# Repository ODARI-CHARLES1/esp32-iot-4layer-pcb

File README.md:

# ESP32 IoT 4-Layer PCB

This project focuses on the design and development of a **4-layer PCB** for an **ESP32-based IoT device**. The goal is to create a compact, robust, and EMI-optimized PCB layout suitable for IoT applications.

---

###### Power Management

###### Microcontroller, USB_UART, FLASH MEMORY AND SD CARD

## Project Overview

- **Microcontroller:** ESP32-WROOM-32 (or compatible module)
- **PCB Layers:** 4 (Signal–Ground–Power–Signal stackup)
- **Purpose:** General-purpose IoT hardware platform for prototyping and deployment
- **Tools Used:** KiCad (v6/v7), Git for version control

---

## Design Highlights

- **4-layer stackup** for improved signal integrity and reduced EMI
- Compact layout with modular headers for sensors and peripherals
- On-board voltage regulation (LDO or buck converter)
- USB-to-UART for programming and debugging
- Decoupling and impedance control best practices
- Optional: Antenna matching network for Wi-Fi/BLE

---

---

## Work in Progress

- [X] Schematic capture
- [X] 4-layer stackup definition
- [x] Final PCB layout
- [x] DRC/clearance verification
- [ ] Gerber export and fabrication
- [ ] Testing and validation

---

## Getting Started

1. Open the project in **KiCad v6 or later**
2. Explore `*.kicad_sch` and `*.kicad_pcb` files
3. Run DRC/ERC checks
4. Generate or review the BOM and Gerbers
5. Export fabrication files for PCB manufacturing

---

## Bill of Materials (BOM)

The complete BOM is available in [`Docs/PROJECT_PCB.csv`](Docs/PROJECT_PCB.csv). This file contains all components required for the PCB assembly, including quantities, values, footprints, and datasheets.

Key components include:

- **ESP32-C3-WROOM-02**: Main microcontroller module
- **CP2102N**: USB-to-UART bridge for programming
- **MCP73871**: Battery charging IC
- **W25Q16JVSS**: 16MB flash memory
- Various capacitors, resistors, LEDs, and connectors

---

## Documentation

- **Schematic PDF**: [`Docs/schematic.pdf`](Docs/schematic.pdf)
- **KiCad Project Files**: See `.kicad_sch` and `.kicad_pcb` files in the repository

---

## Previews

_3D renders, board stackup diagrams, or layout screenshots can go here_

---

## License

This project is open source under the **MIT License** (or specify yours).
Feel free to use, modify, and contribute.

---

## Contributions

Issues, suggestions, and pull requests are welcome!
If you'd like to contribute hardware improvements, please fork and submit a PR.

---

## Contact

Questions or feedback? Reach out via GitHub Issues or email: `daymondodari68@gmail.com`

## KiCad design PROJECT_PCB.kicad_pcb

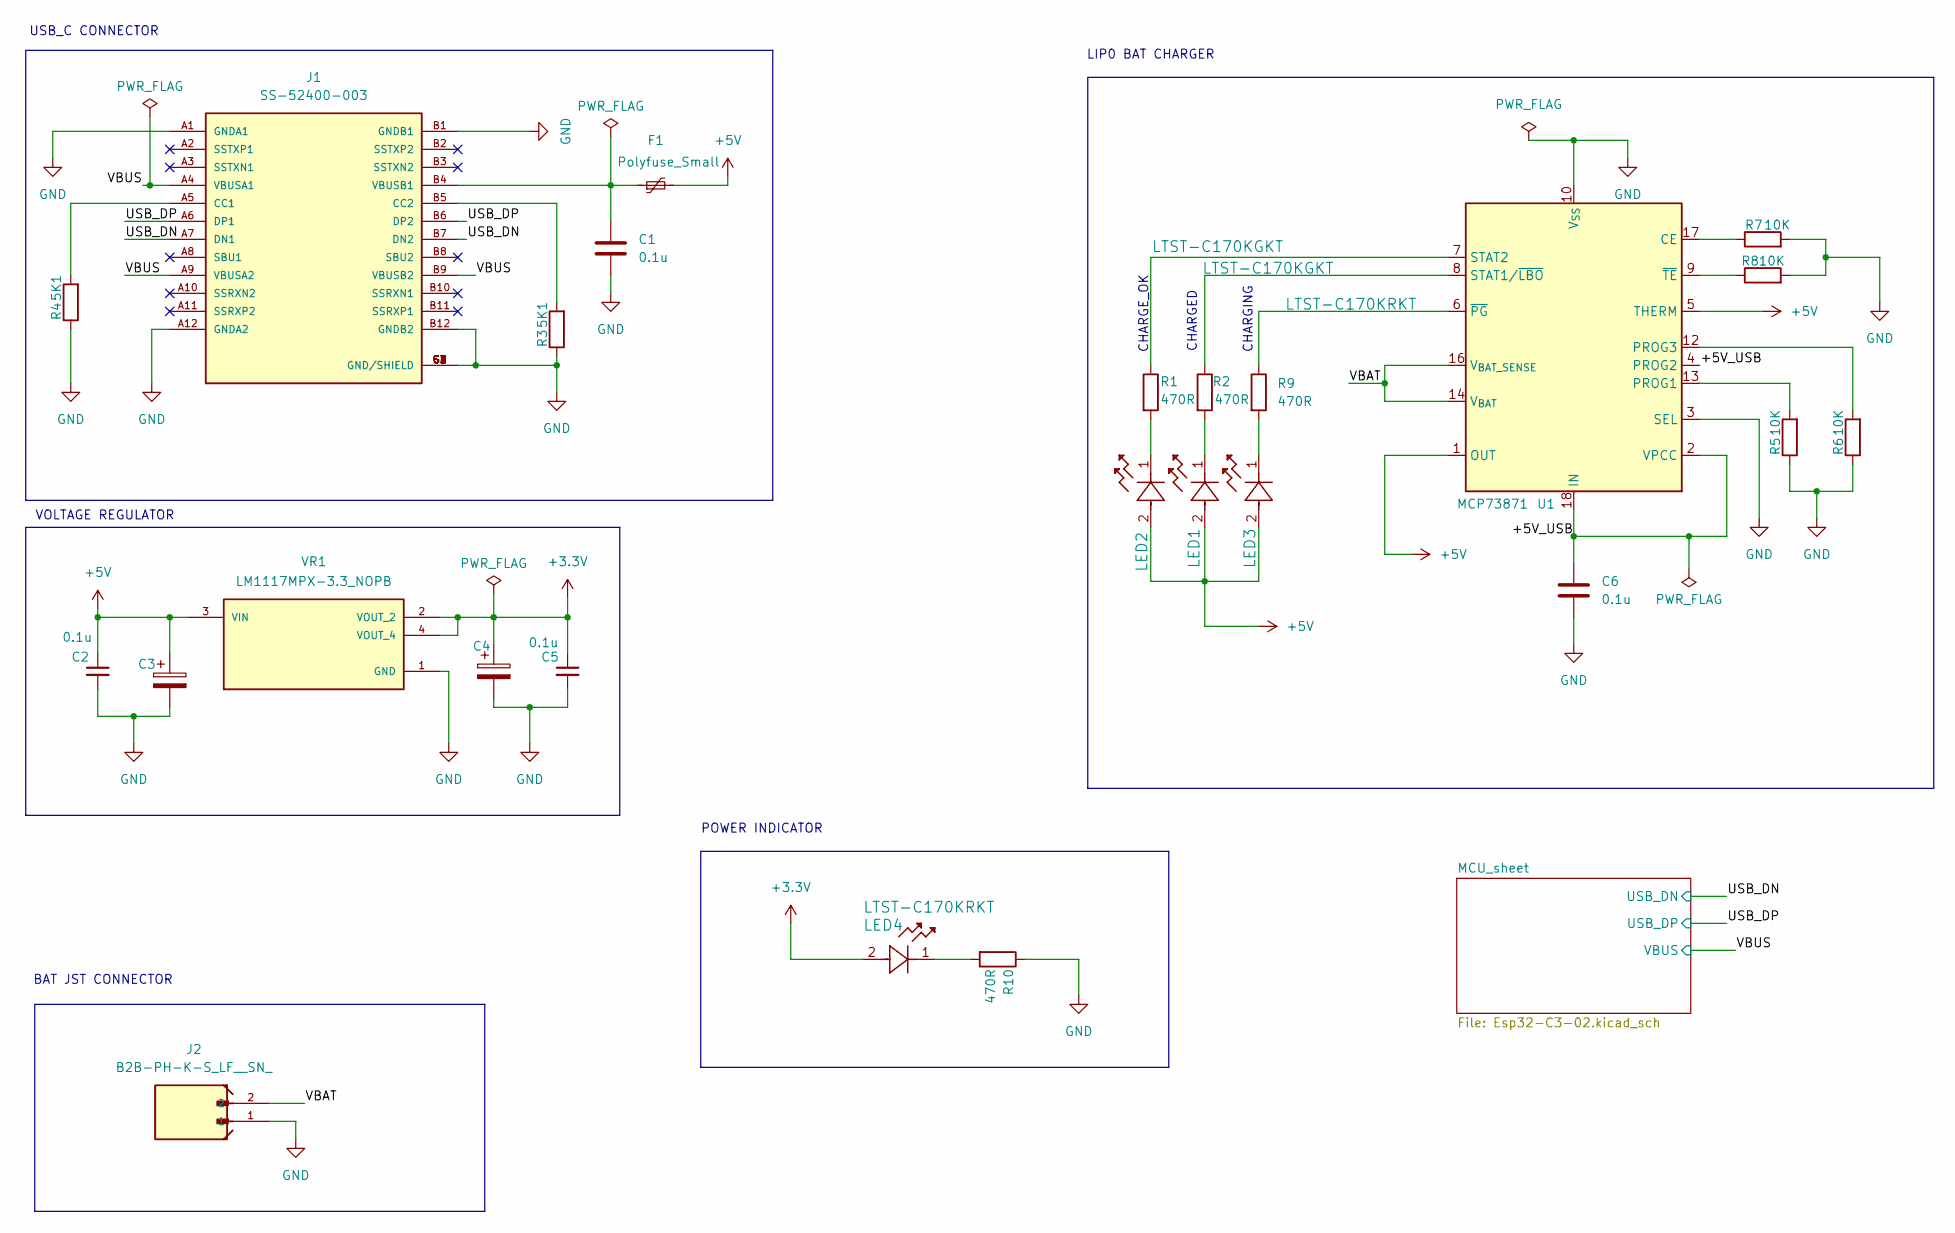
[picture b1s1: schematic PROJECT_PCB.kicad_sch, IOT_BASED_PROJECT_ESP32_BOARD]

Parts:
C1, C2, C5, C6: 0.1u; C_0805_2012Metric
C3, C4: 10u; CAPMP3216X180N
F1: Polyfuse_Small; Fuse_BelFuse_0ZRE0016FF_L9.9mm_W3.8mm
J1: SS-52400-003; BELFUSE_SS-52400-003; Manufacturer part Number SS-52400-003; LCSC C6301911
J2: B2B-PH-K-S_LF__SN_; JST_B2B-PH-K-S_LF__SN_
LED1, LED2: LTST-C170KGKT; LED_0805_2012Metric
LED3, LED4: LTST-C170KRKT; LED_0805_2012Metric
R1, R2, R9, R10: 470R; R_0805_2012Metric
R3, R4: 5K1; R_0805_2012Metric
R5, R6, R7, R8: 10K; R_0805_2012Metric
U1: MCP73871; QFN-20-1EP_4x4mm_P0.5mm_EP2.5x2.5mm
VR1: LM1117MPX-3.3_NOPB; VREG_LM1117MPX-3.3_NOPB; Manufacturer part Number LM1117MPX-3.3/NOPB; LCSC C9662

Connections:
+3.3V: C4.1, C5.1, LED4.2, VR1.2 (VOUT_2), VR1.4 (VOUT_4); also elsewhere on the board
+5V: C2.1, C3.1, F1.2, LED1.2, LED2.2, LED3.2, U1.1 (OUT), U1.5 (THERM), U1.20 (OUT), VR1.3 (VIN)
/+5V_USB: C6.1, U1.2 (VPCC), U1.4 (PROG2), U1.18 (IN), U1.19 (IN)
/USB_DN: J1.A7 (DN1), J1.B7 (DN2); also elsewhere on the board
/USB_DP: J1.A6 (DP1), J1.B6 (DP2); also elsewhere on the board
/VBAT: J2.2, U1.14 (V_{BAT}), U1.15 (V_{BAT}), U1.16 (V_{BAT_SENSE})
/VBUS: J1.A4 (VBUSA1), J1.A9 (VBUSA2), J1.B9 (VBUSB2); also elsewhere on the board
GND: C1.2, C2.2, C3.2, C4.2, C5.2, C6.2, J1.A1 (GNDA1), J1.A12 (GNDA2), J1.B1 (GNDB1), J1.B12 (GNDB2), J1.G1 (GND/SHIELD), J1.G2 (GND/SHIELD), J1.G3 (GND/SHIELD), J1.G4 (GND/SHIELD), J1.S1 (GND/SHIELD), J1.S2 (GND/SHIELD), J1.S3 (GND/SHIELD), J1.S4 (GND/SHIELD), J2.1, R3.1, R4.1, R5.1, R6.1, R7.2, R8.2, R10.1, U1.3 (SEL), U1.10 (V_{SS}), U1.11 (V_{SS}), U1.21 (V_{SS}), VR1.1 (GND); also elsewhere on the board
unnamed: J1.A5 (CC1), R4.2
unnamed: J1.B5 (CC2), R3.2
unnamed: C1.1, F1.1, J1.B4 (VBUSB1)
unnamed: LED1.1, R2.2
unnamed: LED2.1, R1.2
unnamed: LED3.1, R9.2
unnamed: LED4.1, R10.2
unnamed: R7.1, U1.17 (CE)
unnamed: R5.2, U1.13 (PROG1)
unnamed: R6.2, U1.12 (PROG3)
unnamed: R2.1, U1.8 (STAT1/~LBO)
unnamed: R1.1, U1.7 (STAT2)
unnamed: R9.1, U1.6 (~PG)
unnamed: R8.1, U1.9 (~TE)

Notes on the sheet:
LIP0 BAT CHARGER
CHARGE_OK
CHARGED
BAT JST CONNECTOR
VOLTAGE REGULATOR
POWER INDICATOR
CHARGING
USB_C CONNECTOR

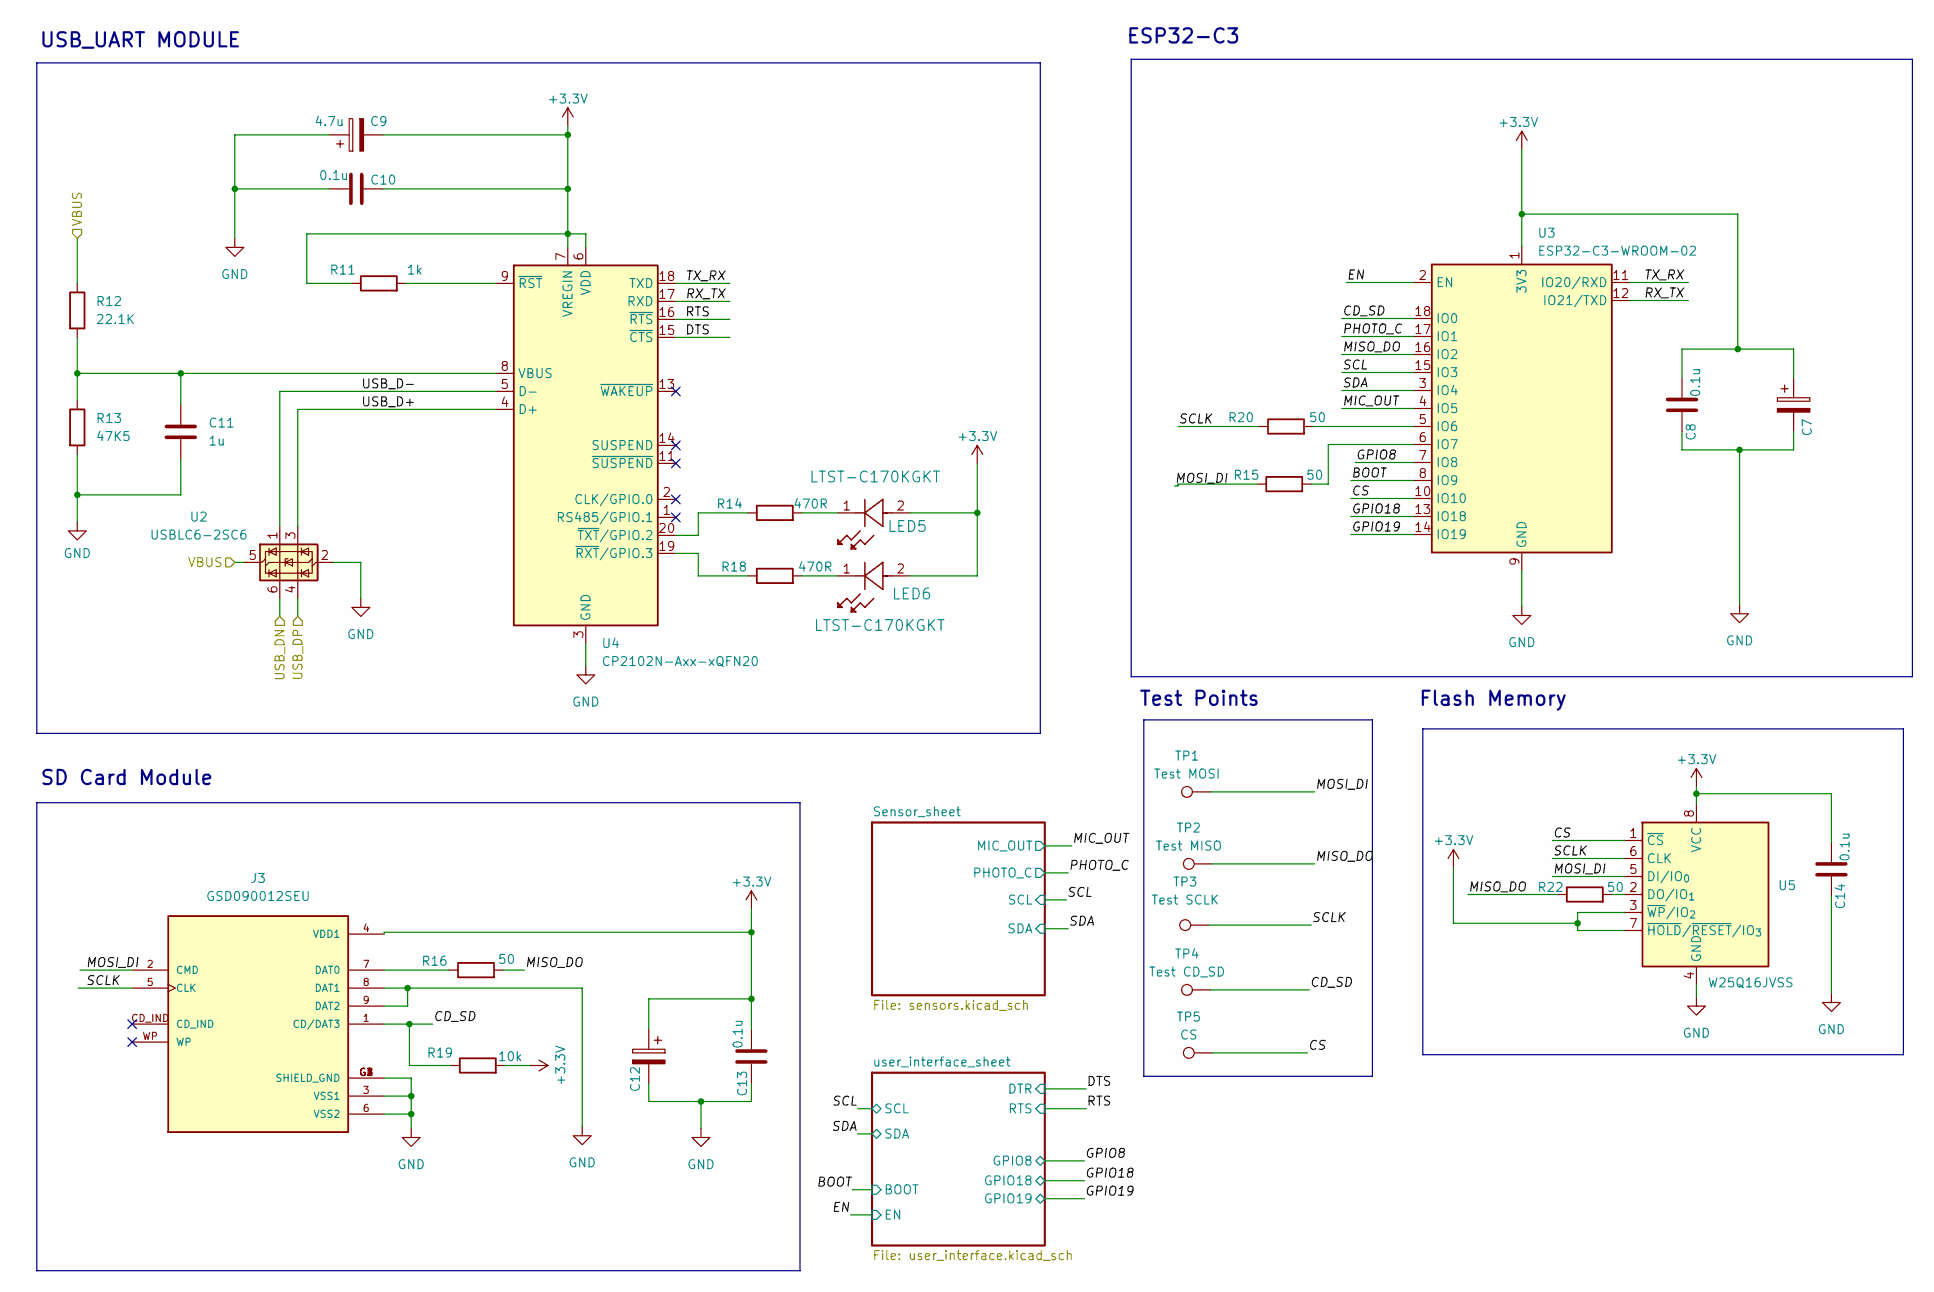
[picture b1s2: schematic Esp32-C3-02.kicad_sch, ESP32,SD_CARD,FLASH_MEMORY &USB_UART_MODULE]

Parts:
C7, C12: 10u; CP_EIA-7343-40_Kemet-Y
C8, C10, C13, C14: 0.1u; C_0805_2012Metric
C9: 4.7u; CP_EIA-7343-40_Kemet-Y
C11: 1u; C_0805_2012Metric
J3: GSD090012SEU; AMPHENOL_GSD090012SEU; PARTREV E
LED5, LED6: LTST-C170KGKT; LED_0805_2012Metric
R11: 1k; R_0805_2012Metric
R12: 22.1K; R_0805_2012Metric
R13: 47K5; R_0805_2012Metric
R14, R18: 470R; R_0805_2012Metric
R15, R16, R20, R22: 50; R_0805_2012Metric
R19: 10k; R_0805_2012Metric
TP1: Test MOSI; TestPoint_Pad_D1.0mm
TP2: Test MISO; TestPoint_Pad_D1.0mm
TP3: Test SCLK; TestPoint_Pad_D1.0mm
TP4: Test CD_SD; TestPoint_Pad_D1.0mm
TP5: CS; TestPoint_Pad_D1.0mm
U2: USBLC6-2SC6; SOT-23-6
U3: ESP32-C3-WROOM-02
U4: CP2102N-Axx-xQFN20; SiliconLabs_QFN-20-1EP_3x3mm_P0.5mm
U5: W25Q16JVSS; SOIC-8_5.3x5.3mm_P1.27mm

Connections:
+3.3V: C7.1, C8.1, C9.2, C10.2, C12.1, C13.1, C14.1, J3.4 (VDD1), LED5.2, LED6.2, R11.1, R19.2, U3.1 (3V3), U4.6 (VDD), U4.7 (VREGIN), U5.3 (~WP/IO_{2}), U5.7 (~HOLD/~RESET/IO_{3}), U5.8 (VCC); also elsewhere on the board
/MCU_sheet/BOOT: U3.8 (IO9); also elsewhere on the board
/MCU_sheet/CD_SD: J3.1 (CD/DAT3), R19.1, TP4.1, U3.18 (IO0)
/MCU_sheet/CS: TP5.1, U3.10 (IO10), U5.1 (~CS)
/MCU_sheet/DTS: U4.15 (~CTS); also elsewhere on the board
/MCU_sheet/EN: U3.2 (EN); also elsewhere on the board
/MCU_sheet/GPIO8: U3.7 (IO8); also elsewhere on the board
/MCU_sheet/GPIO18: U3.13 (IO18); also elsewhere on the board
/MCU_sheet/GPIO19: U3.14 (IO19); also elsewhere on the board
/MCU_sheet/MIC_OUT: U3.4 (IO5); also elsewhere on the board
/MCU_sheet/MISO_DO: R16.2, R22.1, TP2.1, U3.16 (IO2)
/MCU_sheet/MOSI_DI: J3.2 (CMD), R15.1, TP1.1, U5.5 (DI/IO_{0})
/MCU_sheet/PHOTO_C: U3.17 (IO1); also elsewhere on the board
/MCU_sheet/RTS: U4.16 (~RTS); also elsewhere on the board
/MCU_sheet/RX_TX: U3.12 (IO21/TXD), U4.17 (RXD)
/MCU_sheet/SCL: U3.15 (IO3); also elsewhere on the board
/MCU_sheet/SCLK: J3.5 (CLK), R20.1, TP3.1, U5.6 (CLK)
/MCU_sheet/SDA: U3.3 (IO4); also elsewhere on the board
/MCU_sheet/TX_RX: U3.11 (IO20/RXD), U4.18 (TXD)
/MCU_sheet/USB_D+: U2.3 (I/O2), U4.4 (D+)
/MCU_sheet/USB_D-: U2.1 (I/O1), U4.5 (D-)
/USB_DN: U2.6 (I/O1); also elsewhere on the board
/USB_DP: U2.4 (I/O2); also elsewhere on the board
/VBUS: R12.1, U2.5 (VBUS); also elsewhere on the board
GND: C7.2, C8.2, C9.1, C10.1, C11.2, C12.2, C13.2, C14.2, J3.3 (VSS1), J3.6 (VSS2), J3.8 (DAT1), J3.9 (DAT2), J3.G1 (SHIELD_GND), J3.G2 (SHIELD_GND), J3.G3 (SHIELD_GND), J3.G4 (SHIELD_GND), R13.2, U2.2 (GND), U3.9 (GND), U3.19 (GND), U4.3 (GND), U4.12 (GND), U4.21 (GND), U5.4 (GND); also elsewhere on the board
unnamed: J3.7 (DAT0), R16.1
unnamed: LED5.1, R14.2
unnamed: LED6.1, R18.2
unnamed: R20.2, U3.5 (IO6)
unnamed: R15.2, U3.6 (IO7)
unnamed: C11.1, R12.2, R13.1, U4.8 (VBUS)
unnamed: R11.2, U4.9 (~RST)
unnamed: R18.1, U4.19 (~RXT/GPIO.3)
unnamed: R14.1, U4.20 (~TXT/GPIO.2)
unnamed: R22.2, U5.2 (DO/IO_{1})

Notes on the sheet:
SD Card Module
Test Points
USB_UART MODULE
Flash Memory
ESP32-C3

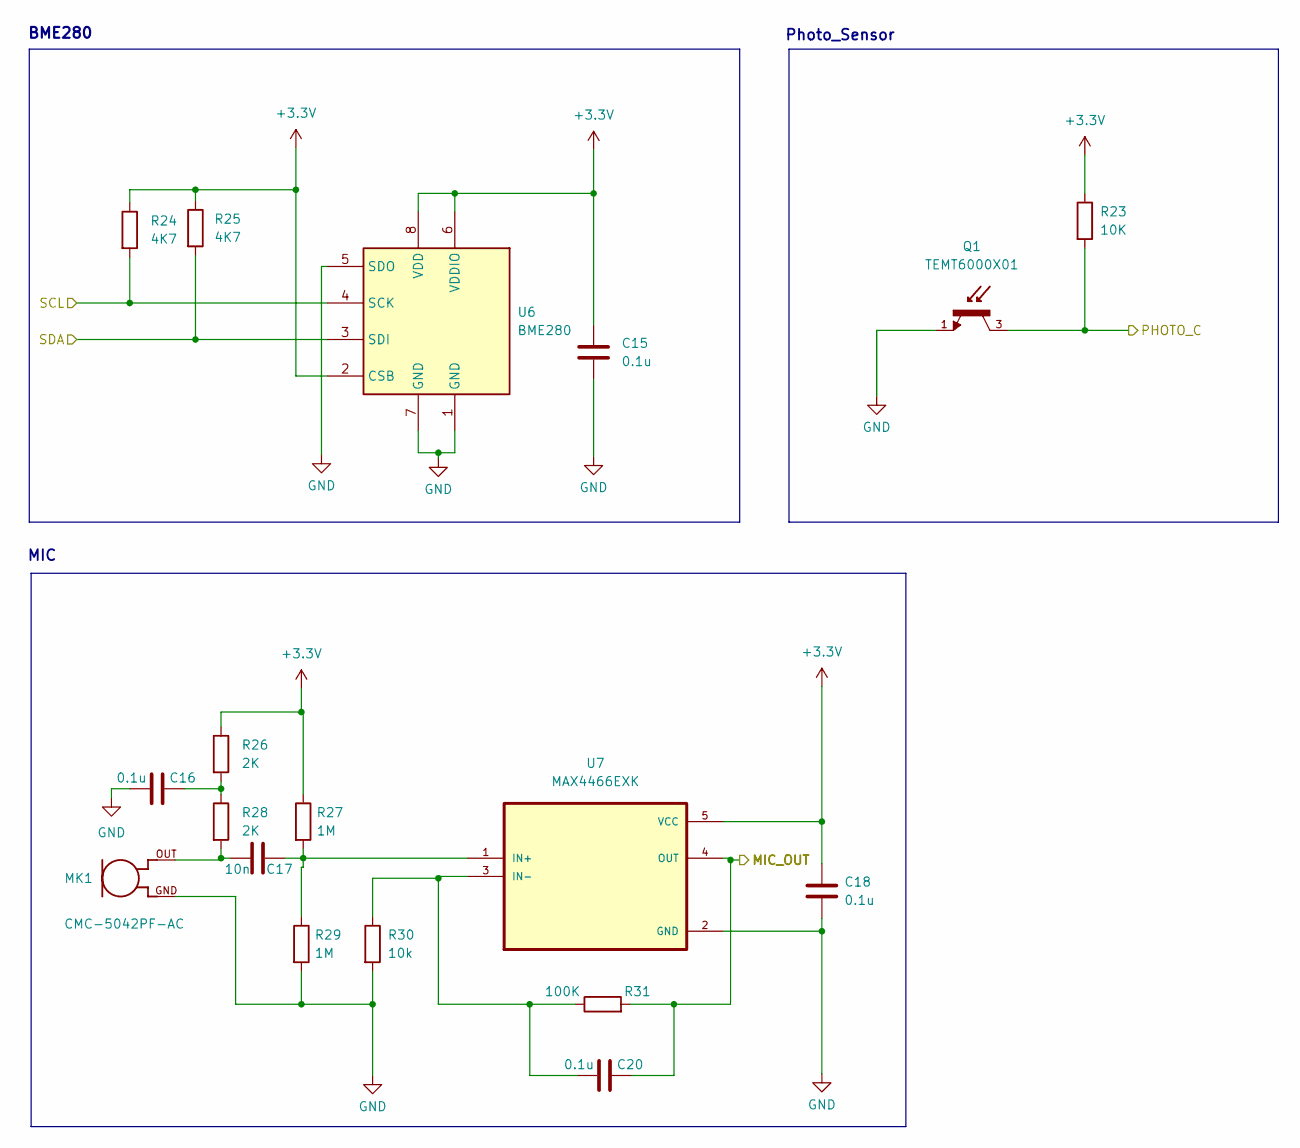
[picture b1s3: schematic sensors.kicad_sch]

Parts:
C15, C16, C18, C20: 0.1u; C_0805_2012Metric
C17: 10n; C_0805_2012Metric
MK1: CMC-5042PF-AC; CUI_CMC-5042PF-AC
Q1: TEMT6000X01; TRANS_TEMT6000X01; PARTREV 1.9
R23: 10K; R_0805_2012Metric
R24, R25: 4K7; R_0805_2012Metric
R26, R28: 2K; R_0805_2012Metric
R27, R29: 1M; R_0805_2012Metric
R30: 10k; R_0805_2012Metric
R31: 100K; R_0805_2012Metric
U6: BME280; Bosch_LGA-8_2.5x2.5mm_P0.65mm_ClockwisePinNumbering
U7: MAX4466EXK; SOT65P210X110-5N

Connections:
+3.3V: C15.1, C18.1, R23.1, R24.1, R25.1, R26.1, R27.1, U6.2 (CSB), U6.6 (VDDIO), U6.8 (VDD), U7.5 (VCC); also elsewhere on the board
/MCU_sheet/MIC_OUT: C20.2, R31.2, U7.4 (OUT); also elsewhere on the board
/MCU_sheet/PHOTO_C: Q1.3, R23.2; also elsewhere on the board
/MCU_sheet/SCL: R24.2, U6.4 (SCK); also elsewhere on the board
/MCU_sheet/SDA: R25.2, U6.3 (SDI); also elsewhere on the board
GND: C15.2, C16.1, C18.2, MK1.GND, Q1.1, R29.2, R30.2, U6.1 (GND), U6.5 (SDO), U6.7 (GND), U7.2 (GND); also elsewhere on the board
unnamed: C16.2, R26.2, R28.1
unnamed: C17.1, MK1.OUT, R28.2
unnamed: C17.2, R27.2, R29.1, U7.1 (IN+)
unnamed: C20.1, R30.1, R31.1, U7.3 (IN-)

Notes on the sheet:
BME280
MIC
Photo_Sensor

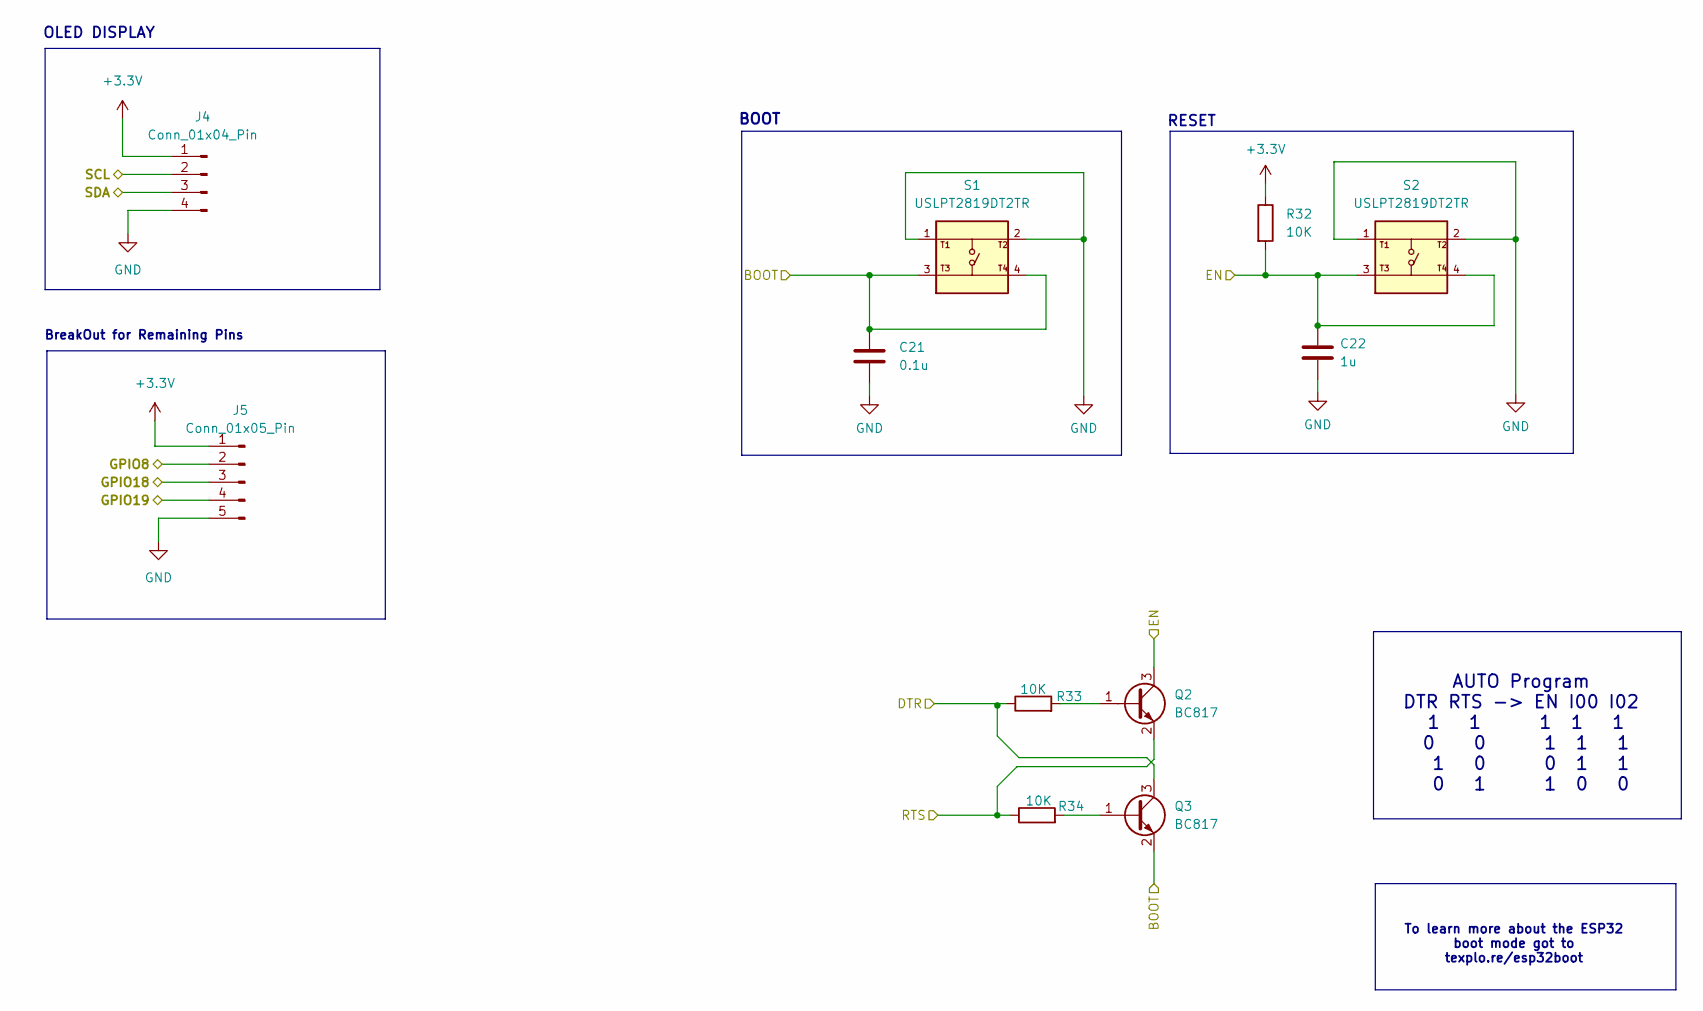
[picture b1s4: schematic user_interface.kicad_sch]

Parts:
C21: 0.1u; C_0805_2012Metric
C22: 1u; C_0805_2012Metric
J4: Conn_01x04_Pin; PinHeader_1x04_P2.54mm_Vertical
J5: Conn_01x05_Pin; PinHeader_1x05_P2.54mm_Vertical
Q2, Q3: BC817; SOT-23
R32, R33, R34: 10K; R_0805_2012Metric
S1, S2: USLPT2819DT2TR; SW_USLPT2819DT2TR; PARTREV P

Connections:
+3.3V: J4.1, J5.1, R32.1; also elsewhere on the board
/MCU_sheet/BOOT: C21.1, Q3.2 (E), S1.3, S1.4; also elsewhere on the board
/MCU_sheet/DTS: Q3.3 (C), R33.1; also elsewhere on the board
/MCU_sheet/EN: C22.1, Q2.3 (C), R32.2, S2.3, S2.4; also elsewhere on the board
/MCU_sheet/GPIO8: J5.2; also elsewhere on the board
/MCU_sheet/GPIO18: J5.3; also elsewhere on the board
/MCU_sheet/GPIO19: J5.4; also elsewhere on the board
/MCU_sheet/RTS: Q2.2 (E), R34.1; also elsewhere on the board
/MCU_sheet/SCL: J4.2; also elsewhere on the board
/MCU_sheet/SDA: J4.3; also elsewhere on the board
GND: C21.2, C22.2, J4.4, J5.5, S1.1, S1.2, S2.1, S2.2; also elsewhere on the board
unnamed: Q2.1 (B), R33.2
unnamed: Q3.1 (B), R34.2

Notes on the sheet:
BreakOut for Remaining Pins
RESET
OLED DISPLAY
AUTO Program DTR RTS -> EN I00 I02 1 1 1 1 1 0 0 1 1 1 1 0 0 1 1 0 1 1 0 0
To learn more about the ESP32 boot mode got to texplo.re/esp32boot
BOOT

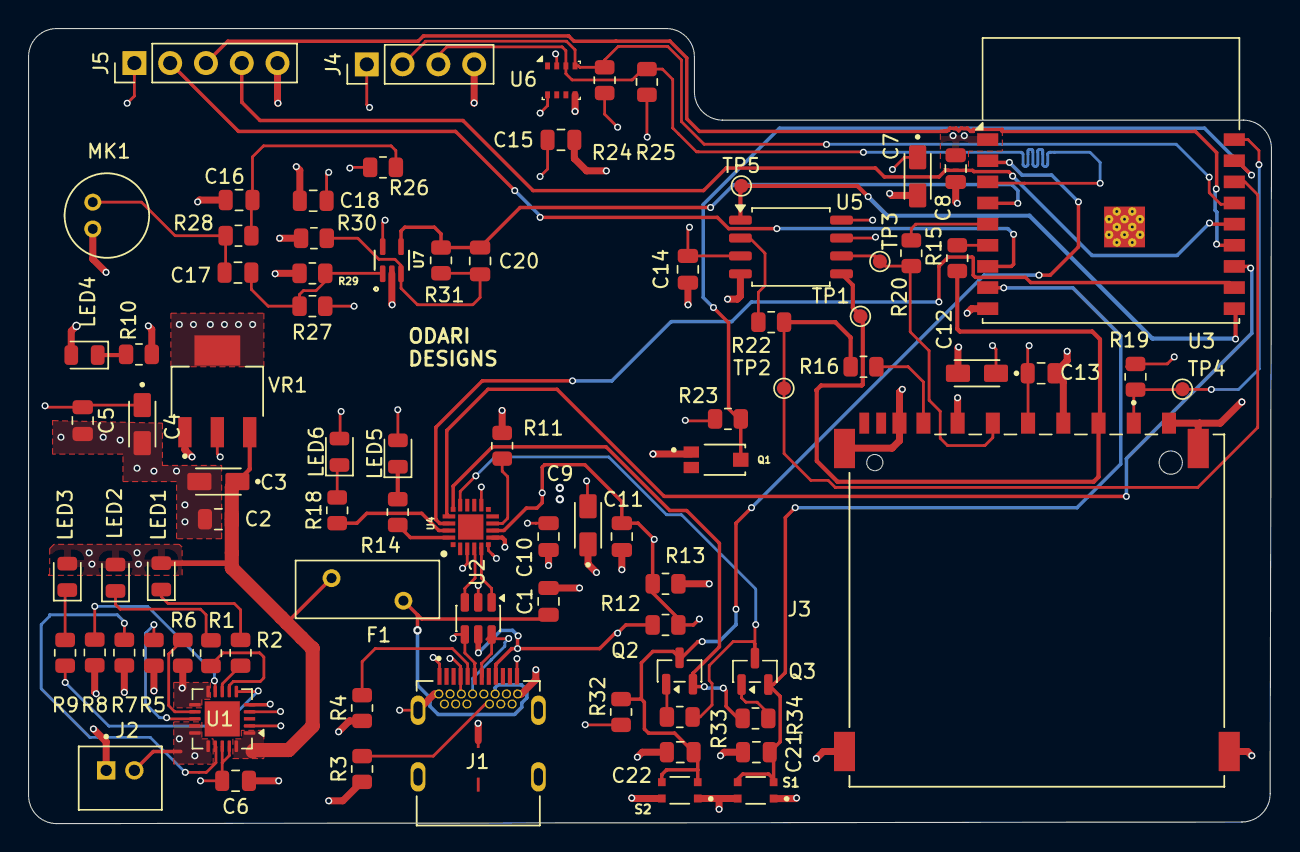
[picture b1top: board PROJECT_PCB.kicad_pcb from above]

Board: 4 copper layers, 88.2 x 56.4 mm, 84 parts (0 on the bottom side), 58 nets.

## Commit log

2025-07-07 updated gitignore
2025-07-15 schematic additons
2025-07-16 Schematic update
2025-07-31 esp32 circuitry design
2025-07-31 modification to the first sheet
2025-11-03 update added schematic to Readme
2025-11-03 initial commit schematic snapshot
2025-11-03 Initial commit docs schematic pdf
2025-11-03 update added esp32,uart , sd card and flash memory schematic
2025-11-04 final touch on esp32-wroom-02 , flash memory, sd_card,testpoints & USB_UART schematic
2025-11-04 initial commit sensor schematic sheet
2025-11-04 initial commit user_interface
2025-11-04 update root schematic sheet
2025-11-04 update sensor schematic
2025-11-10 implementationo of the BME280 sensor
2025-11-14 initial commit user-interface schematic
2025-11-14 connecting hierarchial Pins
2025-11-17 finish up on user interface schematic capture
2025-11-24 update schematic
2025-11-24 ignored file
2025-11-24 update the mcu sheet
2025-11-24 modified the kicad_sh-back file
2025-11-24 modified kicard_prl file
2025-11-24 update the main file schematic
2025-11-24 final touch on user interface schematic
2025-11-24 final touch on project project_pcb.kicad_sch-bak
2025-12-12 run ERC check for the schematic
2025-12-12 initial commit tantulum capacitor T491 symbol , footprint and 3d model
2025-12-12 update gitignore to allow .step files for components
2025-12-12 added pcb layout of the project
2025-12-15 assigning footprint, pcb setup and configurations
2025-12-22 updat schematic adding missing capacitor c19
2025-12-22 PCB outlining and component placement
2025-12-22 add fuse footprint
2025-12-22 add symbol
2026-02-05 routing pcb
2026-02-11 update pcb layout
2026-02-15 final update on pcb layout
2026-02-16 add .gitignore extension files
2026-02-16 update pcb-layout
2026-02-16 generate gerber.zip file
2026-02-16 PCB 3D view
2026-03-02 update the symbol information for manufacturing suite
